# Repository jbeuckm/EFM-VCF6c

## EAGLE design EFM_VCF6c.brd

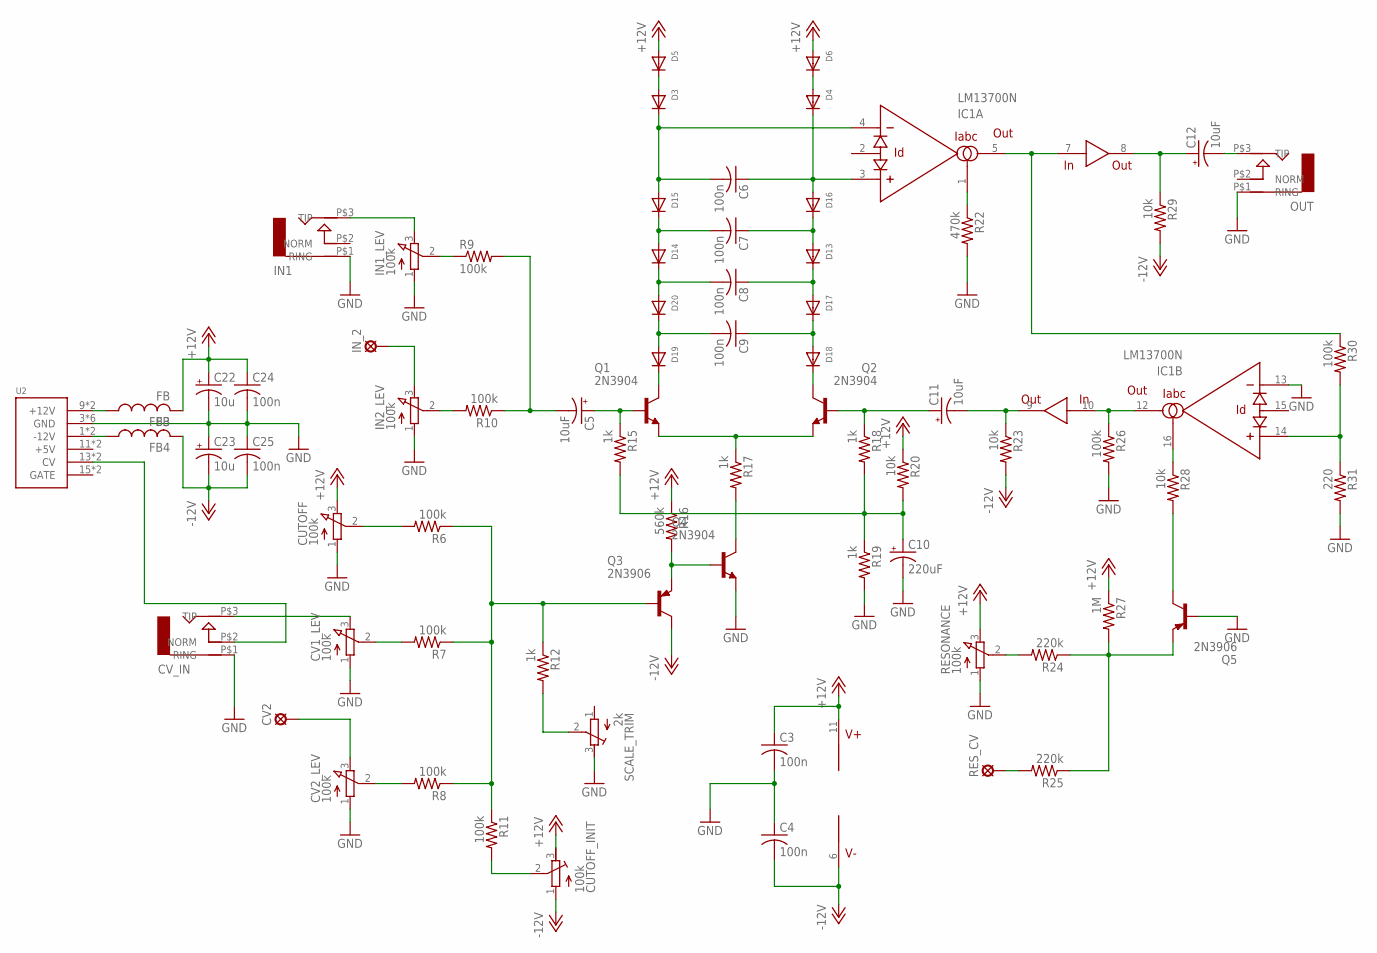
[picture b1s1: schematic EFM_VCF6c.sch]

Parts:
C3, C4: 100n; C1206
C5, C11, C12: 10uF; B45181A
C6, C7, C8, C9: 100n; C025-030X050
C10: 220uF; B45181A
C22, C23: 10u; B45181A
C24, C25: 100n; C050-024X044
CUTOFF: 100k; PTD901
CUTOFF_INIT: 100k; RTRIM64W
CV1_LEV, CV2_LEV: 100k; PTD901
CV2: LSP10
CV_IN: AUDIO-JACKITEAD; JACK-90DEG-ITEAD
D3, D4, D5, D6, D13, D14, D15, D16, D17, D18, D19, D20: DIODEDO-1N4148; DO-1N4148
FB3, FB4: FB
IC1: LM13700N; DIL16
IN1: AUDIO-JACKITEAD; JACK-90DEG-ITEAD
IN1_LEV, IN2_LEV: 100k; PTD901
IN_2: LSP10
OUT: AUDIO-JACKITEAD; JACK-90DEG-ITEAD
Q1, Q2, Q4: 2N3904; TO92
Q3, Q5: 2N3906; TO92
R6, R7, R8, R9, R10, R11, R26, R30: 100k; 0207/7
R12, R15, R17, R18, R19: 1k; 0207/7
R16: 560k; 0207/7
R20, R23, R28, R29: 10k; 0207/7
R22: 470k; 0207/7
R24, R25: 220k; 0207/7
R27: 1M; 0207/7
R31: 220; 0207/7
RESONANCE: 100k; PTD901
RES_CV: LSP10
SCALE_TRIM: 2k; RTRIM64W
U2: POWER; POWER_16

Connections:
+12V: C22.+, C24.1, FB3.P$2 (2)
-12V: C4.2, C23.-, C25.2, CUTOFF_INIT.1 (A), FB4.P$2 (2), IC1.6 (V-), Q3.1 (C), R23.2, R29.2
GND: C3.2, C4.1, C10.-, C22.-, C23.+, C24.2, C25.1, CUTOFF.1 (A), CV1_LEV.1 (A), CV2_LEV.1 (A), CV_IN.P$1 (RING), IC1.13 (-IN), IN1.P$1 (RING), IN1_LEV.1 (A), IN2_LEV.1 (A), OUT.P$1 (RING), Q4.3 (E), Q5.2 (B), R19.2, R22.2, R26.2, R31.2, RESONANCE.1 (A), SCALE_TRIM.3 (E), U2.3 (GND), U2.4 (GND), U2.5 (GND), U2.6 (GND), U2.7 (GND), U2.8 (GND)
unnamed: IC1.1 (IABC), R22.1
unnamed: R25.2, RES_CV.MP
unnamed: Q4.1 (C), R17.2
unnamed: Q1.3 (E), Q2.3 (E), R17.1
unnamed: IN2_LEV.2 (S), R10.2
unnamed: C5.-, R9.2, R10.1
unnamed: C5.+, Q1.2 (B), R15.1
unnamed: Q3.3 (E), Q4.2 (B), R16.2
unnamed: C6.2, D3.C, D15.A, IC1.4 (-IN)
unnamed: CV2_LEV.2 (S), R8.2
unnamed: IC1.5 (OUT), IC1.7 (IN), R30.1
unnamed: C6.1, D4.C, D16.A, IC1.3 (+IN)
unnamed: C7.1, D13.A, D16.C
unnamed: C8.2, D14.C, D20.A
unnamed: C8.1, D13.C, D17.A
unnamed: Q3.2 (B), R6.1, R7.1, R8.1, R11.1, R12.1
unnamed: C9.1, D17.C, D18.A
unnamed: C9.2, D19.A, D20.C
unnamed: D19.C, Q1.1 (C)
unnamed: D18.C, Q2.1 (C)
unnamed: D3.A, D5.C
unnamed: D4.A, D6.C
unnamed: R24.2, RESONANCE.2 (S)
unnamed: Q5.3 (E), R24.1, R25.1, R27.2
unnamed: C10.+, R15.2, R18.2, R19.1, R20.2
unnamed: C11.+, Q2.2 (B), R18.1
unnamed: CUTOFF_INIT.2 (S), R11.2
unnamed: C12.+, IC1.8 (OUT), R29.1
unnamed: C7.2, D14.A, D15.C
unnamed: IC1.14 (+IN), R30.2, R31.1
unnamed: C12.-, OUT.P$3 (TIP)
unnamed: IC1.16 (IABC), R28.1
unnamed: Q5.1 (C), R28.2
unnamed: IN2_LEV.3 (E), IN_2.MP
unnamed: C11.-, IC1.9 (OUT), R23.1
unnamed: IC1.10 (IN), IC1.12 (OUT), R26.1
unnamed: R12.2, SCALE_TRIM.2 (S)
unnamed: C3.1, CUTOFF.3 (E), CUTOFF_INIT.3 (E), D5.A, D6.A, IC1.11 (V+), R16.1, R20.1, R27.1, RESONANCE.3 (E)
unnamed: CV_IN.P$2 (NORM), U2.13 (CV), U2.14 (CV)
unnamed: FB3.P$1 (1), U2.9 (+12V), U2.10 (+12V)
unnamed: CV1_LEV.2 (S), R7.2
unnamed: CV2.MP, CV2_LEV.3 (E)
unnamed: CUTOFF.2 (S), R6.2
unnamed: IN1_LEV.2 (S), R9.1
unnamed: IN1.P$3 (TIP), IN1_LEV.3 (E)
unnamed: CV1_LEV.3 (E), CV_IN.P$3 (TIP)
unnamed: FB4.P$1 (1), U2.1 (-12V), U2.2 (-12V)

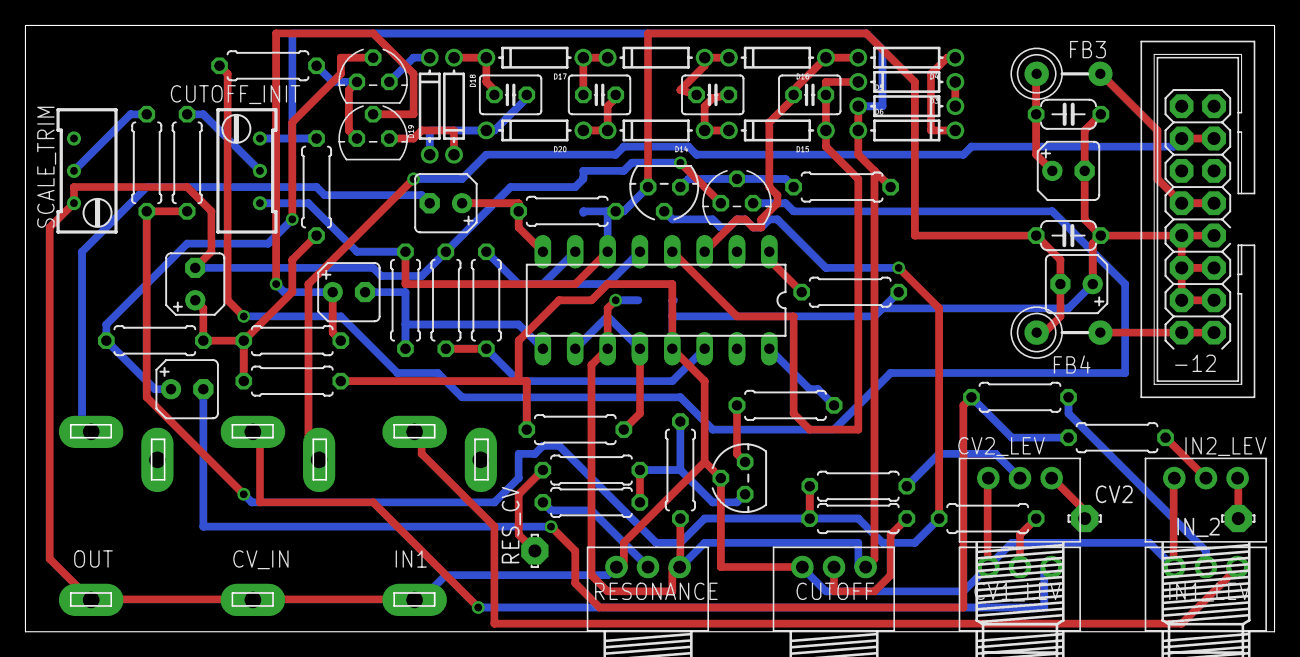
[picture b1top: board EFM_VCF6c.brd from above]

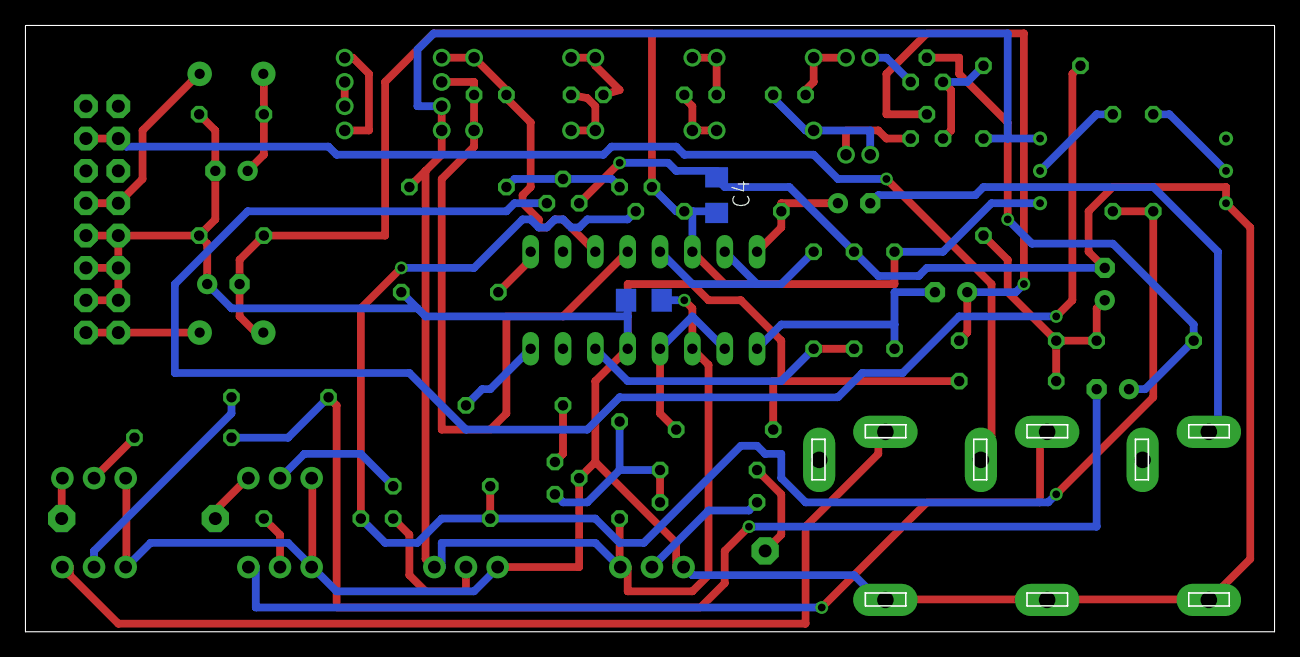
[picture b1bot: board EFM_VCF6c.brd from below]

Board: 2 copper layers, 98.1 x 47.6 mm, 72 parts (2 on the bottom side), 50 nets.

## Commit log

2015-10-08 schemo progress
2015-10-08 layout begins
2015-10-08 layout close
2015-10-09 ready to test cut
2015-10-11 fix and mod for self res
2015-10-11 fixed cv range setting r16
2015-10-12 spread out pots and added panel
2017-09-01 added gitignore
2017-09-01 updated power and pots and better diodes
2017-09-01 routed and labels adjusted
